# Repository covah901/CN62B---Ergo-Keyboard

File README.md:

# CN62B - Ergo Keyboard 
AtMega32A Ergo keyboard based on CFTKB's Mysterium
https://imgur.com/a/Je4tYqu

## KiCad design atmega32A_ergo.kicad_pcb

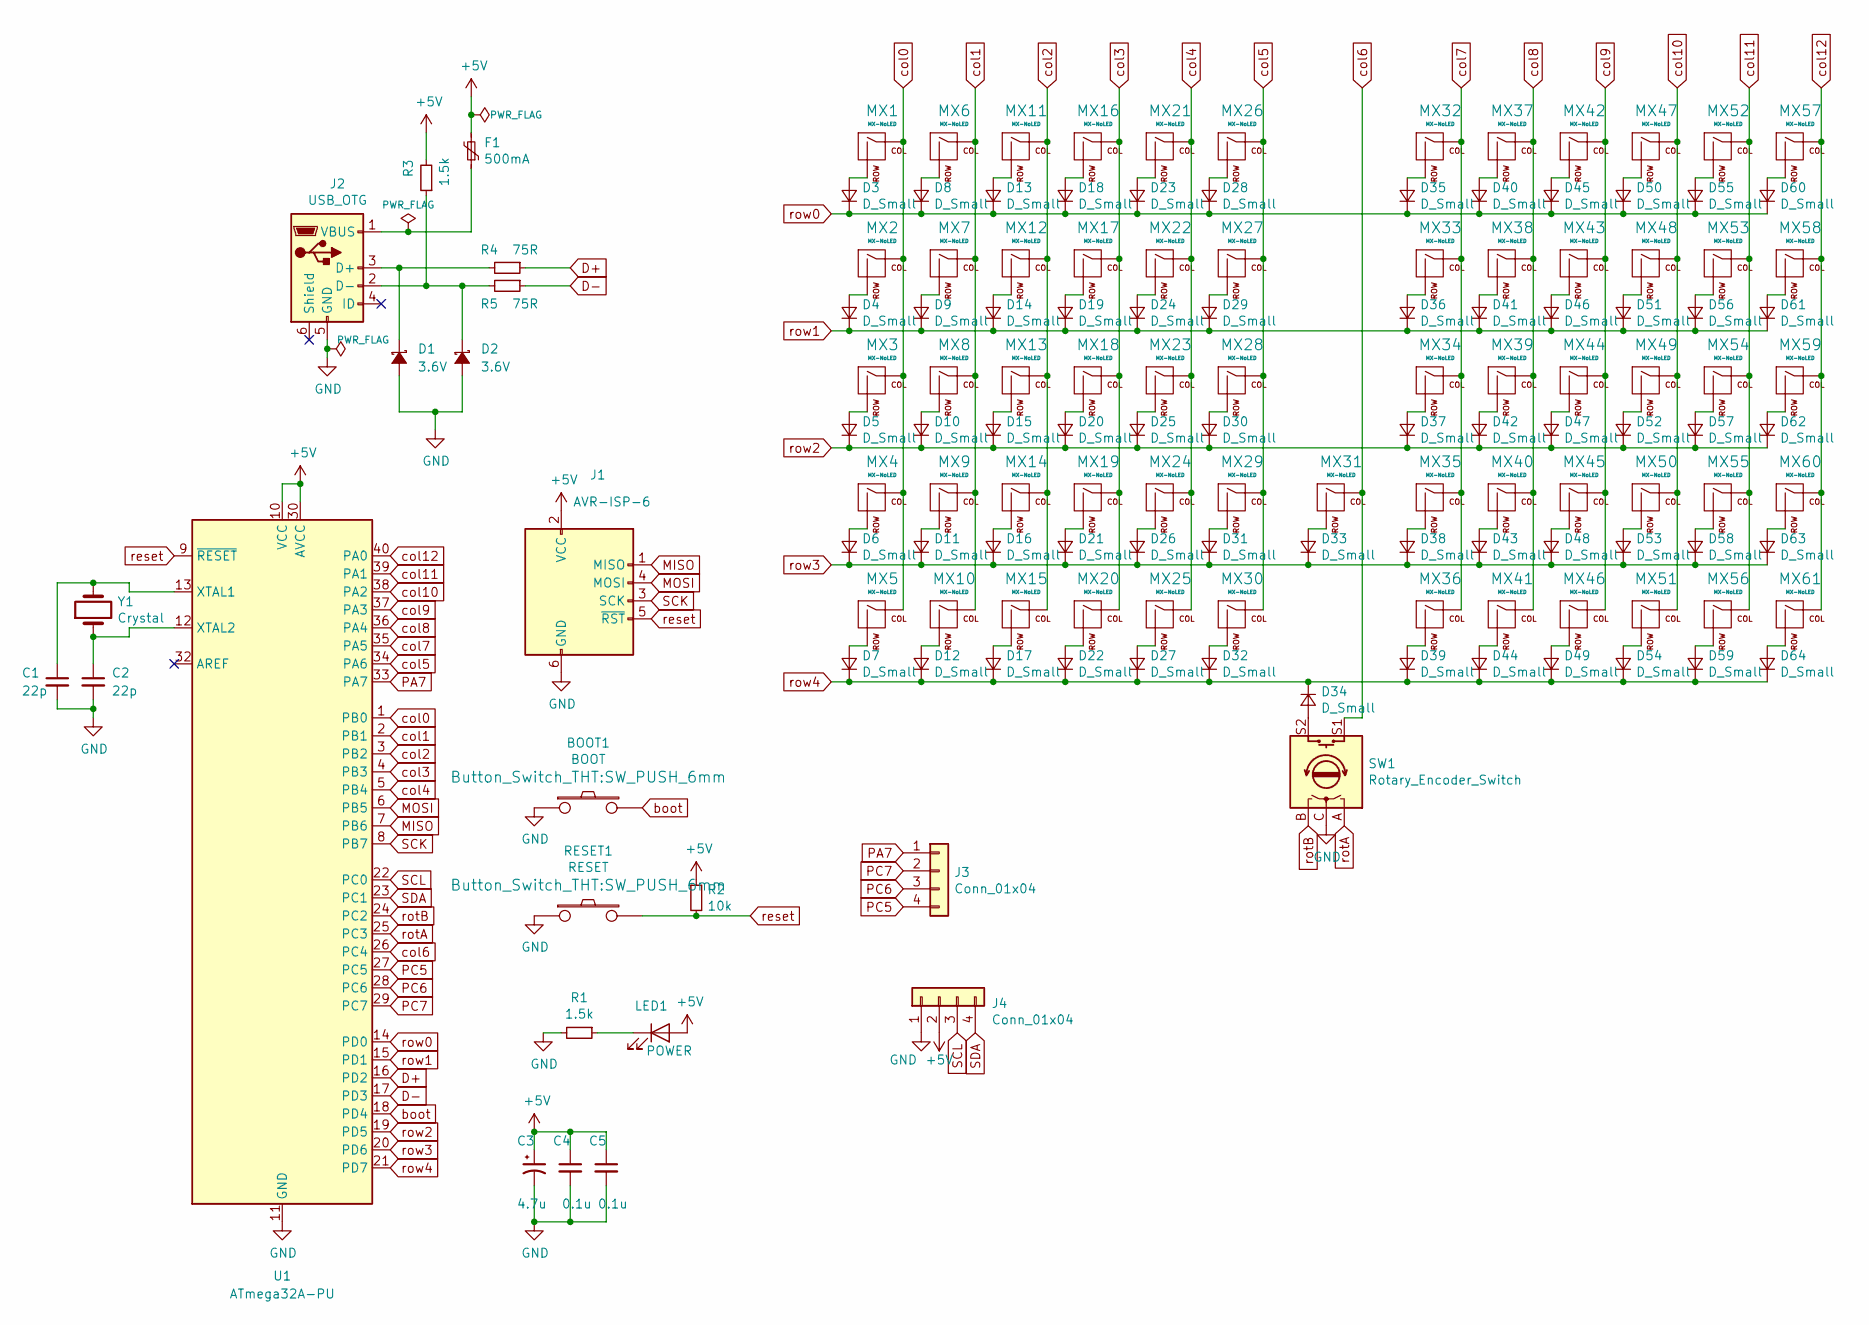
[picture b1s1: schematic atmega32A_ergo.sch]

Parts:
BOOT1: BOOT; SW_PUSH_6mm
C1, C2: 22p; C_Disc_D3.0mm_W1.6mm_P2.50mm
C3: 4.7u; CP_Radial_D4.0mm_P1.50mm
C4, C5: 0.1u; C_Disc_D4.3mm_W1.9mm_P5.00mm
D1, D2: 3.6V; D_DO-35_SOD27_P5.08mm_Vertical_AnodeUp
D3, D4, D5, D6, D7, D8, D9, D10, D11, D12, D13, D14, D15, D16, D17, D18, D19, D20, D21, D22, D23, D24, D25, D26, D27, D28, D29, D30, D31, D32, D33, D34, D35, D36, D37, D38, D39, D40, D41, D42, D43, D44, D45, D46, D47, D48, D49, D50, D51, D52, D53, D54, D55, D56, D57, D58, D59, D60, D61, D62, D63, D64: D_Small; Diode_Long
F1: 500mA; polyfuse_5.1mm
J1: AVR-ISP-6; AVR_ICSP_3x2
J2: USB_OTG; USB-Mini-B_ LCSC-C46398
J3, J4: Conn_01x04; PinHeader_1x04_P2.54mm_Vertical
LED1: POWER; LED_D3.0mm
MX1, MX2, MX3, MX4, MX5, MX6, MX7, MX8, MX9, MX10, MX11, MX12, MX13, MX14, MX15, MX16, MX17, MX18, MX19, MX20, MX21, MX22, MX23, MX24, MX25, MX26, MX27, MX28, MX29, MX30, MX31, MX32, MX33, MX34, MX35, MX36, MX37, MX38, MX39, MX40, MX41, MX42, MX43, MX44, MX45, MX46, MX47, MX48, MX49, MX50, MX51, MX52, MX53, MX54, MX55, MX56, MX57, MX58, MX59, MX60, MX61: MX-NoLED; MX_PCB_100H
R1, R3: 1.5k; R_Axial_DIN0204_L3.6mm_D1.6mm_P7.62mm_Horizontal
R2: 10k; R_Axial_DIN0204_L3.6mm_D1.6mm_P7.62mm_Horizontal
R4, R5: 75R; R_Axial_DIN0204_L3.6mm_D1.6mm_P7.62mm_Horizontal
RESET1: RESET; SW_PUSH_6mm
SW1: Rotary_Encoder_Switch; RotaryEncoder_Alps_EC11E-Switch_Vertical_H20mm
U1: ATmega32A-PU; DIP-40_W15.24mm
Y1: Crystal; Crystal_HC49-4H_Vertical

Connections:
+5V: C3.1, C4.1, C5.1, F1.2, J1.2 (VCC), J4.2, LED1.2 (A), R2.1, R3.2, U1.10 (VCC), U1.30 (AVCC); also elsewhere on the board
D+: R4.1, U1.16 (PD2)
D-: R5.1, U1.17 (PD3)
GND: BOOT1.1, C1.2, C2.2, C3.2, C4.2, C5.2, D1.2 (A), D2.2 (A), J1.6 (GND), J2.5 (GND), J4.1, R1.2, RESET1.1, SW1.C, U1.11 (GND), U1.31 (GND); also elsewhere on the board
MISO: J1.1 (MISO), U1.7 (PB6)
MOSI: J1.4 (MOSI), U1.6 (PB5)
unnamed: C1.1, U1.13 (XTAL1), Y1.2
unnamed: C2.1, U1.12 (XTAL2), Y1.1
unnamed: D1.1 (K), J2.3 (D+), R4.2
unnamed: D2.1 (K), J2.2 (D-), R3.1, R5.2
unnamed: D3.2 (A), MX1.2 (ROW)
unnamed: D4.2 (A), MX2.2 (ROW)
unnamed: D5.2 (A), MX3.2 (ROW)
unnamed: D6.2 (A), MX4.2 (ROW)
unnamed: D7.2 (A), MX5.2 (ROW)
unnamed: D8.2 (A), MX6.2 (ROW)
unnamed: D9.2 (A), MX7.2 (ROW)
unnamed: D10.2 (A), MX8.2 (ROW)
unnamed: D11.2 (A), MX9.2 (ROW)
unnamed: D12.2 (A), MX10.2 (ROW)
unnamed: D13.2 (A), MX11.2 (ROW)
unnamed: D14.2 (A), MX12.2 (ROW)
unnamed: D15.2 (A), MX13.2 (ROW)
unnamed: D16.2 (A), MX14.2 (ROW)
unnamed: D17.2 (A), MX15.2 (ROW)
unnamed: D18.2 (A), MX16.2 (ROW)
unnamed: D19.2 (A), MX17.2 (ROW)
unnamed: D20.2 (A), MX18.2 (ROW)
unnamed: D21.2 (A), MX19.2 (ROW)
unnamed: D22.2 (A), MX20.2 (ROW)
unnamed: D23.2 (A), MX21.2 (ROW)
unnamed: D24.2 (A), MX22.2 (ROW)
unnamed: D25.2 (A), MX23.2 (ROW)
unnamed: D26.2 (A), MX24.2 (ROW)
unnamed: D27.2 (A), MX25.2 (ROW)
unnamed: D28.2 (A), MX26.2 (ROW)
unnamed: D29.2 (A), MX27.2 (ROW)
unnamed: D30.2 (A), MX28.2 (ROW)
unnamed: D31.2 (A), MX29.2 (ROW)
unnamed: D32.2 (A), MX30.2 (ROW)
unnamed: D33.2 (A), MX31.2 (ROW)
unnamed: D34.2 (A), SW1.S2
unnamed: D35.2 (A), MX32.2 (ROW)
unnamed: D36.2 (A), MX33.2 (ROW)
unnamed: D37.2 (A), MX34.2 (ROW)
unnamed: D38.2 (A), MX35.2 (ROW)
unnamed: D39.2 (A), MX36.2 (ROW)
unnamed: D40.2 (A), MX37.2 (ROW)
unnamed: D41.2 (A), MX38.2 (ROW)
unnamed: D42.2 (A), MX39.2 (ROW)
unnamed: D43.2 (A), MX40.2 (ROW)
unnamed: D44.2 (A), MX41.2 (ROW)
unnamed: D45.2 (A), MX42.2 (ROW)
unnamed: D46.2 (A), MX43.2 (ROW)
unnamed: D47.2 (A), MX44.2 (ROW)
unnamed: D48.2 (A), MX45.2 (ROW)
unnamed: D49.2 (A), MX46.2 (ROW)
unnamed: D50.2 (A), MX47.2 (ROW)
unnamed: D51.2 (A), MX48.2 (ROW)
unnamed: D52.2 (A), MX49.2 (ROW)
unnamed: D53.2 (A), MX50.2 (ROW)
unnamed: D54.2 (A), MX51.2 (ROW)
unnamed: D55.2 (A), MX52.2 (ROW)
unnamed: D56.2 (A), MX53.2 (ROW)
unnamed: D57.2 (A), MX54.2 (ROW)
unnamed: D58.2 (A), MX55.2 (ROW)
unnamed: D59.2 (A), MX56.2 (ROW)
unnamed: D60.2 (A), MX57.2 (ROW)
unnamed: D61.2 (A), MX58.2 (ROW)
unnamed: D62.2 (A), MX59.2 (ROW)
unnamed: D63.2 (A), MX60.2 (ROW)
unnamed: D64.2 (A), MX61.2 (ROW)
unnamed: F1.1, J2.1 (VBUS)
unnamed: LED1.1 (K), R1.1
PA7: J3.1, U1.33 (PA7)
PC5: J3.4, U1.27 (PC5)
PC6: J3.3, U1.28 (PC6)
PC7: J3.2, U1.29 (PC7)
SCK: J1.3 (SCK), U1.8 (PB7)
SCL: J4.3, U1.22 (PC0); also elsewhere on the board
SDA: J4.4, U1.23 (PC1); also elsewhere on the board
boot: BOOT1.2, U1.18 (PD4)
col0: MX1.1 (COL), MX2.1 (COL), MX3.1 (COL), MX4.1 (COL), MX5.1 (COL), U1.1 (PB0)
col1: MX6.1 (COL), MX7.1 (COL), MX8.1 (COL), MX9.1 (COL), MX10.1 (COL), U1.2 (PB1)
col2: MX11.1 (COL), MX12.1 (COL), MX13.1 (COL), MX14.1 (COL), MX15.1 (COL), U1.3 (PB2)
col3: MX16.1 (COL), MX17.1 (COL), MX18.1 (COL), MX19.1 (COL), MX20.1 (COL), U1.4 (PB3)
col4: MX21.1 (COL), MX22.1 (COL), MX23.1 (COL), MX24.1 (COL), MX25.1 (COL), U1.5 (PB4)
col5: MX26.1 (COL), MX27.1 (COL), MX28.1 (COL), MX29.1 (COL), MX30.1 (COL), U1.34 (PA6)
col6: MX31.1 (COL), SW1.S1, U1.26 (PC4)
col7: MX32.1 (COL), MX33.1 (COL), MX34.1 (COL), MX35.1 (COL), MX36.1 (COL), U1.35 (PA5)
col8: MX37.1 (COL), MX38.1 (COL), MX39.1 (COL), MX40.1 (COL), MX41.1 (COL), U1.36 (PA4)
col9: MX42.1 (COL), MX43.1 (COL), MX44.1 (COL), MX45.1 (COL), MX46.1 (COL), U1.37 (PA3)
col10: MX47.1 (COL), MX48.1 (COL), MX49.1 (COL), MX50.1 (COL), MX51.1 (COL), U1.38 (PA2)
col11: MX52.1 (COL), MX53.1 (COL), MX54.1 (COL), MX55.1 (COL), MX56.1 (COL), U1.39 (PA1)
col12: MX57.1 (COL), MX58.1 (COL), MX59.1 (COL), MX60.1 (COL), MX61.1 (COL), U1.40 (PA0)
reset: J1.5 (~RST), R2.2, RESET1.2, U1.9 (~RESET)
rotA: SW1.A, U1.25 (PC3)
rotB: SW1.B, U1.24 (PC2)
row0: D3.1 (K), D8.1 (K), D13.1 (K), D18.1 (K), D23.1 (K), D28.1 (K), D35.1 (K), D40.1 (K), D45.1 (K), D50.1 (K), D55.1 (K), D60.1 (K), U1.14 (PD0)
row1: D4.1 (K), D9.1 (K), D14.1 (K), D19.1 (K), D24.1 (K), D29.1 (K), D36.1 (K), D41.1 (K), D46.1 (K), D51.1 (K), D56.1 (K), D61.1 (K), U1.15 (PD1)
row2: D5.1 (K), D10.1 (K), D15.1 (K), D20.1 (K), D25.1 (K), D30.1 (K), D37.1 (K), D42.1 (K), D47.1 (K), D52.1 (K), D57.1 (K), D62.1 (K), U1.19 (PD5)
row3: D6.1 (K), D11.1 (K), D16.1 (K), D21.1 (K), D26.1 (K), D31.1 (K), D33.1 (K), D38.1 (K), D43.1 (K), D48.1 (K), D53.1 (K), D58.1 (K), D63.1 (K), U1.20 (PD6)
row4: D7.1 (K), D12.1 (K), D17.1 (K), D22.1 (K), D27.1 (K), D32.1 (K), D34.1 (K), D39.1 (K), D44.1 (K), D49.1 (K), D54.1 (K), D59.1 (K), D64.1 (K), U1.21 (PD7)

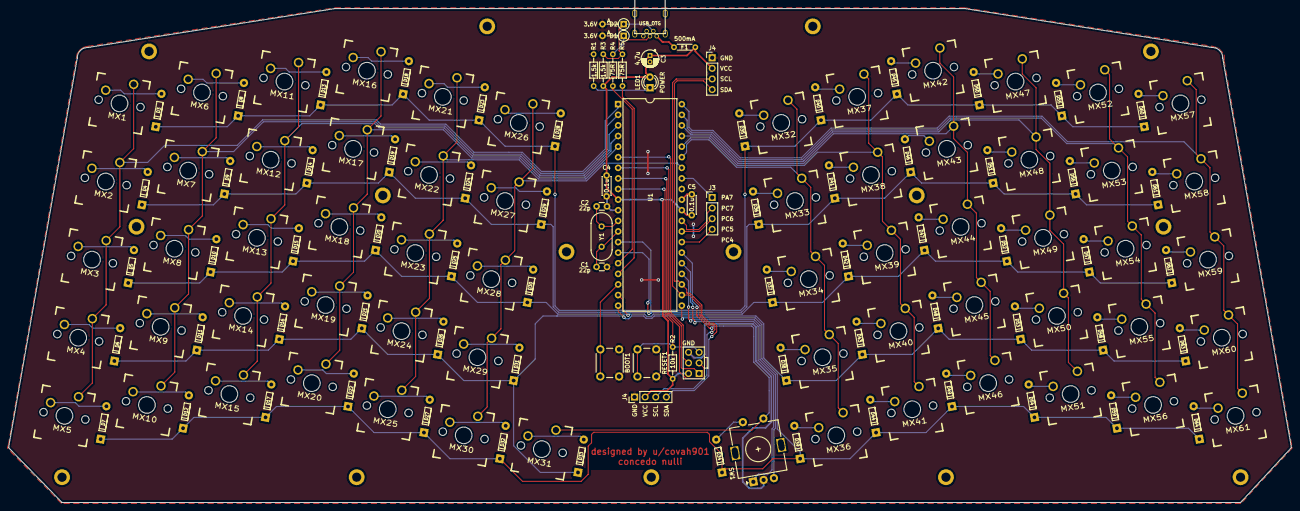
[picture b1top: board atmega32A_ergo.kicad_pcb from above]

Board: 2 copper layers, 307.3 x 118.3 mm, 147 parts (0 on the bottom side), 103 nets.

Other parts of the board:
J4#2: Conn_01x04; PinHeader_1x04_P2.54mm_Vertical

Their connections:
+5V: J4#2.2; also elsewhere on the board
GND: J4#2.1; also elsewhere on the board
SCL: J4#2.3; also elsewhere on the board
SDA: J4#2.4; also elsewhere on the board

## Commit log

2020-08-19 Update keymap.c
    made encoder have different function in different layers
